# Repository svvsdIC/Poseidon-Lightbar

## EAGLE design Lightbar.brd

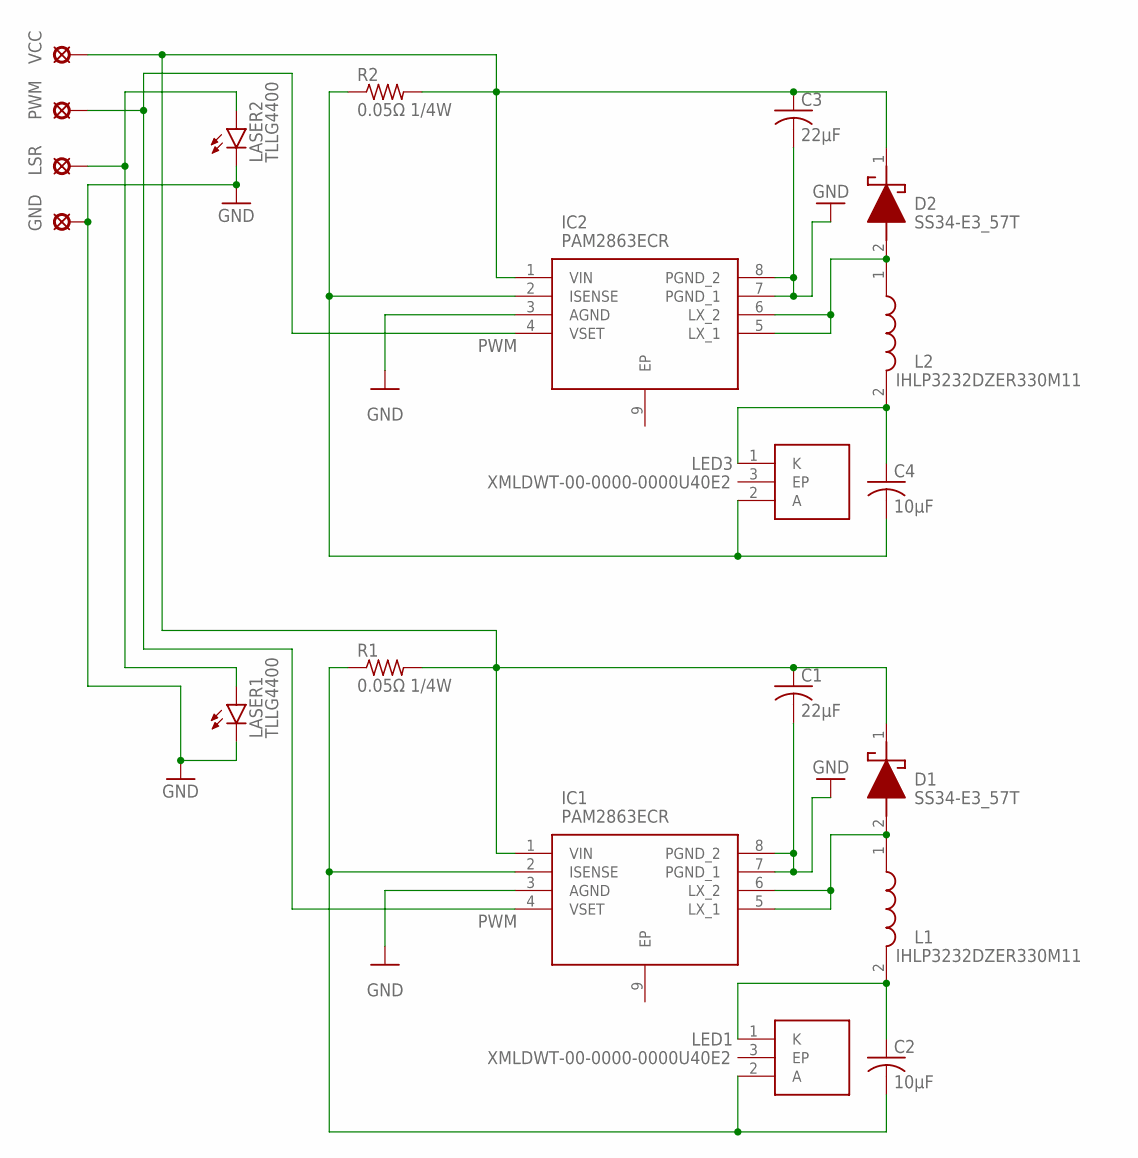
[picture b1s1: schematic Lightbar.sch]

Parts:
C1, C3: 22μF; C1210
C2, C4: 10μF; C1210
D1, D2: SS34-E3_57T; DIOM7959X262N
GND: LSP10
IC1, IC2: PAM2863ECR; SOIC127P600X175-9N
L1, L2: IHLP3232DZER330M11
LASER1, LASER2: TLLG4400; LED3MM
LED1, LED3: XMLDWT-00-0000-0000U40E2; XMLDWT0000000000U40E2
LSR: LSP10
PWM: LSP10
R1, R2: 0.05Ω 1/4W; R0805
VCC: LSP10

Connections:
GND: C1.2, C3.2, GND.MP, IC1.3 (AGND), IC1.7 (PGND_1), IC1.8 (PGND_2), IC2.3 (AGND), IC2.7 (PGND_1), IC2.8 (PGND_2), LASER1.K (C), LASER2.K (C)
unnamed: C2.1, L1.2, LED1.1 (K)
unnamed: C2.2, IC1.2 (ISENSE), LED1.2 (A), R1.1
unnamed: C1.1, C3.1, D1.1 (K), D2.1 (K), IC1.1 (VIN), IC2.1 (VIN), R1.2, R2.2, VCC.MP
unnamed: D1.2 (A), IC1.5 (LX_1), IC1.6 (LX_2), L1.1
unnamed: D2.2 (A), IC2.5 (LX_1), IC2.6 (LX_2), L2.1
unnamed: C4.1, L2.2, LED3.1 (K)
unnamed: C4.2, IC2.2 (ISENSE), LED3.2 (A), R2.1
unnamed: LASER1.A, LASER2.A, LSR.MP
PWM1: IC1.4 (VSET), IC2.4 (VSET), PWM.MP

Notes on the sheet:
PWM

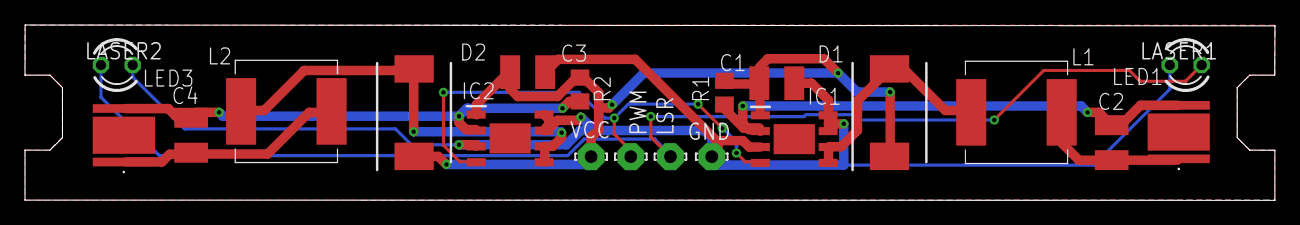
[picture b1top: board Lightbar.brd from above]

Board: 2 copper layers, 100.0 x 14.0 mm, 20 parts (0 on the bottom side), 10 nets.

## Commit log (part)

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2023-09-28 Create Lightbar Schematic
    The schematic created from the previous two meetings, should be ready to prototype.
2023-10-08 Create Fusion 360 Projects
    Designed Fusion 360 boards from EAGLE schematic. Two versions are included, one with a narrow PCB and another with a square PCB.
2023-10-11 Create Schematic Image
    Quick schematic screenshot for prototypes without needing Fusion 360.
2023-10-25 Create Polygons and Reworks
    After talking with mechanical, it seems like the long PCB would be best. I created polygon layers, which don't carry any power, but could be ground in the future. Added a few other adjustments too. I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
2023-11-06 Create Dual Circuit Board
    Finished a new PCB with two on circuits with one board and connection. Even narrower than previous long board, and was made with the requirements to be 9 cm long or less. Also fixes the trace width a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
2023-11-30 Changed File Organization and Names
2023-12-03 Write PWM and Laser Code
2024-02-26 Added notches and screw holes
2024-02-28 Adjust screw hole size
2024-09-04 Removed Holes
2025-03-05 Sensor Board Update
    I also forgot what I updated here :((
2025-03-06 updated lightbar
    added resistors and transistor
2025-03-12 reworked laser system
2025-03-13 Create Final Gerber Finals
